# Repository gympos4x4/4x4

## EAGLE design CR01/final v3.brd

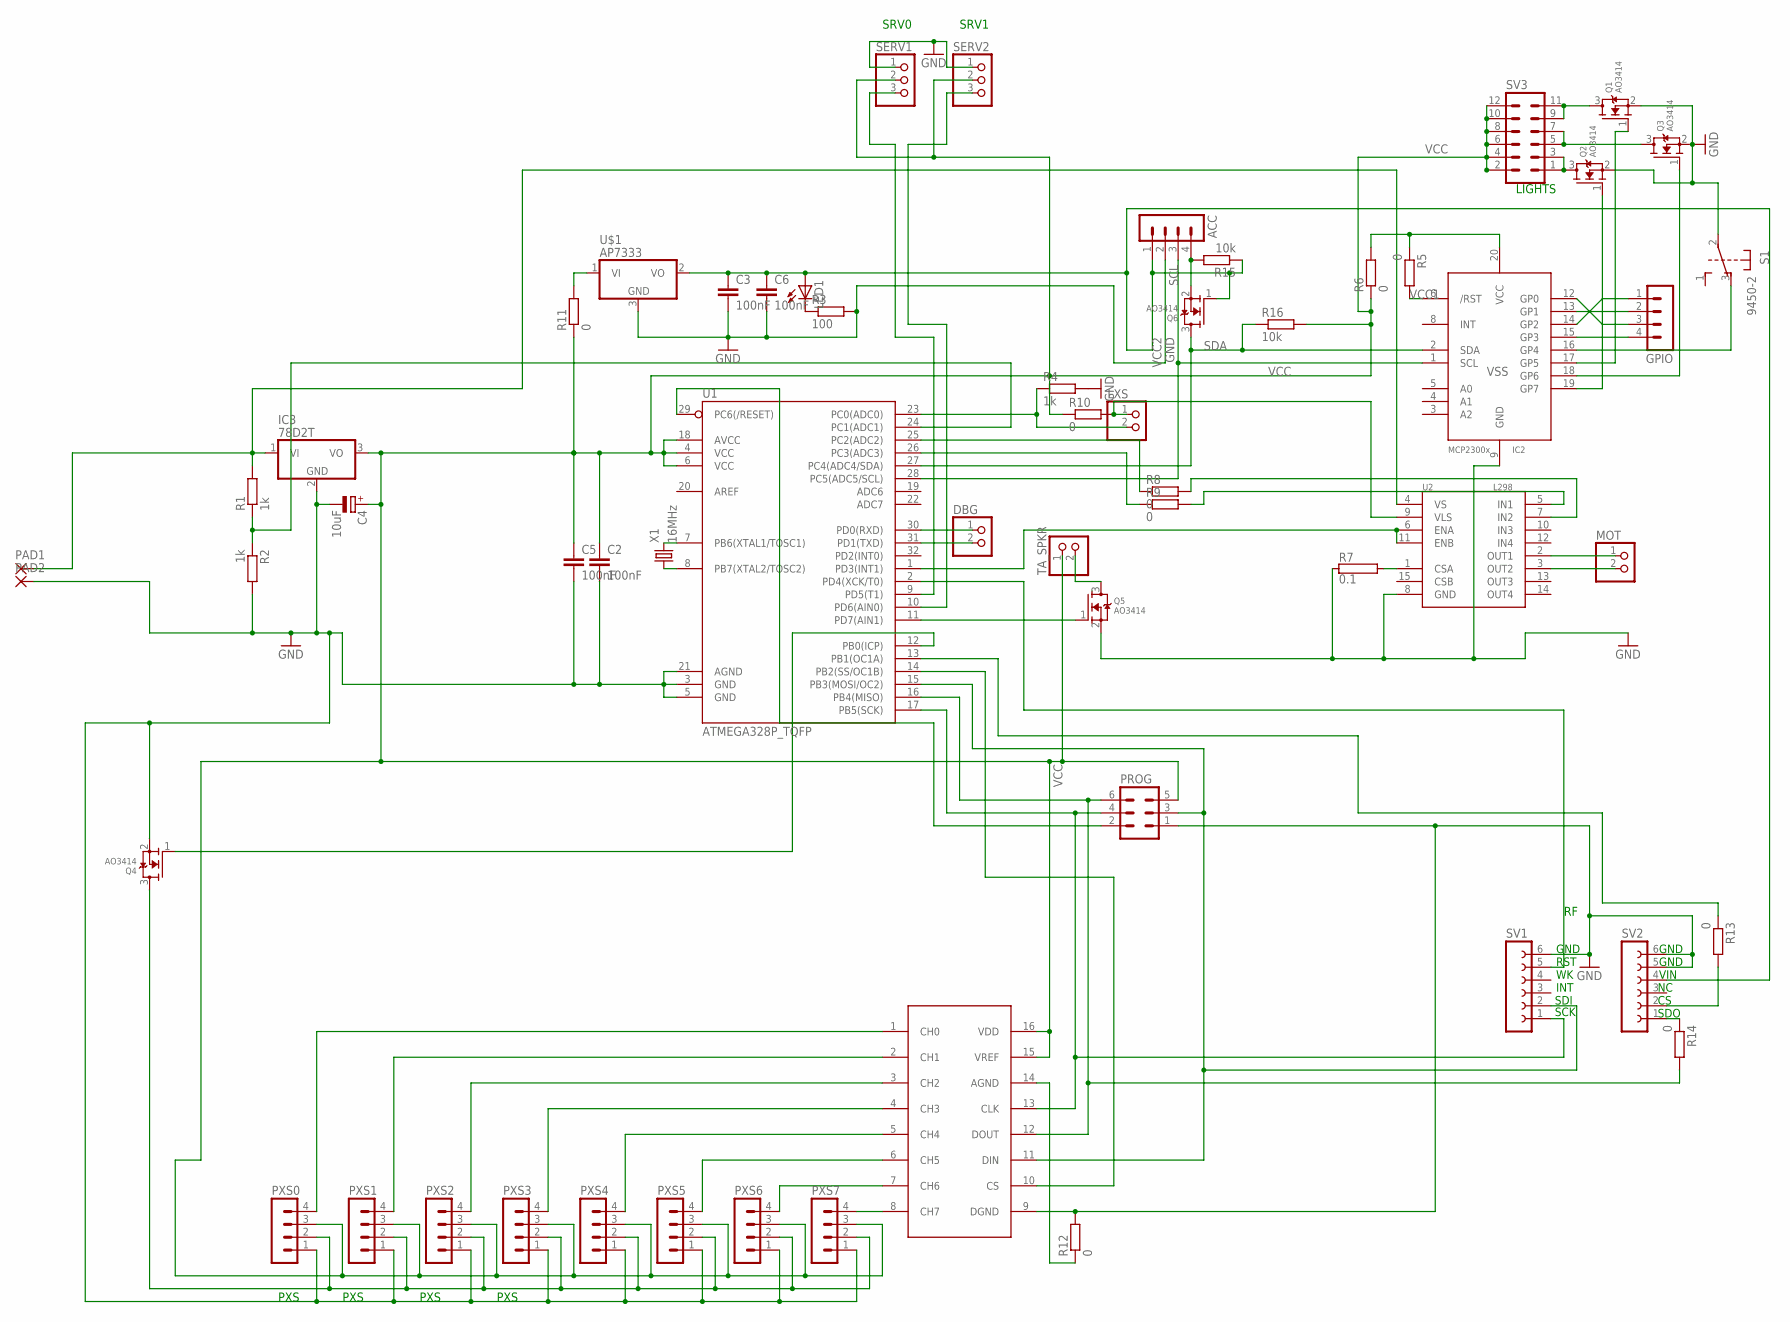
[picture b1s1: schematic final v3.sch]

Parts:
ACC: MA04-1
C2, C3, C5, C6: 100nF; C1206
C4: 10uF; 153CLV-0505
DBG: PINHD-1X2; 1X02
GPIO: MA04-1
IC2: MCP23008/SS; SSOP20
IC3: 78D2T; D2PACK
LED1: LEDCHIPLED_0603; CHIPLED_0603
LXS: PINHD-1X2; 1X02
MOT: PINHD-1X2; 1X02
PAD1, PAD2: SMD5; SMD2,54-5,08
PROG: MA03-2
PXS0, PXS1, PXS2, PXS3, PXS4, PXS5, PXS6, PXS7: MA04-1
Q1, Q2, Q3, Q4, Q5, Q6: AO3414; SOT23
R1, R4: 1k; M1206
R2: 1k; R1206
R3: 100; R0603
R5, R6, R8, R9, R10, R11, R12, R13, R14: 0; R0805BR
R7: 0.1; KH208R-8
R15, R16: 10k; R0805BR
S1: 9450-2
SERV1, SERV2: PINHD-1X3; 1X03
SV1, SV2: FE06-1; FE06
SV3: MA06-2
TA_SPKR: PINHD-1X2; 1X02
U1: ATMEGA328P_TQFP; TQFP32-08
U2: L298; MULTIWATT15
U$1: AP7333; SOT23
U$3: MCP3208; SO-16
X1: 16MHz; HC49/S

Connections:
!RST: PROG.2, U1.29 (PC6(/RESET))
GND: ACC.2, C2.2, C3.2, C4.-, C5.2, C6.2, IC2.9 (GND), IC3.2 (GND), PAD2.1, PROG.1, PXS0.1, PXS1.1, PXS2.1, PXS3.1, PXS4.1, PXS5.1, PXS6.1, PXS7.1, Q1.2 (S), Q2.2 (S), Q3.2 (S), Q4.2 (S), Q5.2 (S), R2.2, R3.2, R4.2, R7.1, R12.2, S1.2, SERV1.1, SERV2.1, SV1.6, SV2.5, SV2.6, U1.3 (GND), U1.5 (GND), U1.21 (AGND), U2.8 (GND), U$1.3 (GND), U$3.9 (DGND)
MISO: PROG.6, R14.2, U1.16 (PB4(MISO)), U$3.12 (DOUT)
MOSI: PROG.3, SV1.2, U1.15 (PB3(MOSI/OC2)), U$3.11 (DIN)
M_EN: U1.1 (PD3(INT1)), U2.6 (ENA), U2.11 (ENB)
M_IN1: R8.2, U2.7 (IN2)
M_IN2: R9.1, U1.26 (PC3(ADC3))
unnamed: Q5.1 (G), U1.11 (PD7(AIN1))
unnamed: Q5.3 (D), TA_SPKR.2
unnamed: U1.14 (PB2(SS/OC1B)), U$3.10 (CS)
unnamed: Q1.3 (D), SV3.9, SV3.11
unnamed: DBG.1, U1.30 (PD0(RXD))
unnamed: PXS7.4, U$3.8 (CH7)
unnamed: MOT.1, U2.2 (OUT1)
unnamed: PXS6.4, U$3.7 (CH6)
unnamed: PXS5.4, U$3.6 (CH5)
unnamed: DBG.2, U1.31 (PD1(TXD))
unnamed: PXS4.4, U$3.5 (CH4)
unnamed: PXS3.4, U$3.4 (CH3)
unnamed: PXS2.4, U$3.3 (CH2)
unnamed: PXS1.4, U$3.2 (CH1)
unnamed: Q3.3 (D), SV3.5, SV3.7
unnamed: PXS0.4, U$3.1 (CH0)
unnamed: Q2.3 (D), SV3.1, SV3.3
unnamed: LXS.2, R4.1, U1.23 (PC0(ADC0))
unnamed: Q4.1 (G), U1.12 (PB0(ICP))
unnamed: PXS0.2, PXS1.2, PXS2.2, PXS3.2, PXS4.2, PXS5.2, PXS6.2, PXS7.2, Q4.3 (D)
unnamed: ACC.4, Q6.2 (S), R15.2
unnamed: MOT.2, U2.3 (OUT2)
unnamed: LED1.C, R3.1
unnamed: R8.1, U1.25 (PC2(ADC2))
unnamed: R9.2, U2.5 (IN1)
unnamed: SV1.5, U1.2 (PD4(XCK/T0))
unnamed: IC2.20 (VCC), R5.1, R6.2
unnamed: SERV1.3, U1.9 (PD5(T1))
unnamed: U1.7 (PB6(XTAL1/TOSC1)), X1.2
unnamed: IC2.19 (GP7), Q2.1 (G)
unnamed: SERV2.3, U1.10 (PD6(AIN0))
unnamed: IC2.17 (GP5), Q1.1 (G)
unnamed: IC2.18 (GP6), Q3.1 (G)
unnamed: U1.8 (PB7(XTAL2/TOSC2)), X1.1
unnamed: R7.2, U2.1 (CSA)
unnamed: IC2.16 (GP4), S1.3 (O)
unnamed: GPIO.3, IC2.12 (GP0)
unnamed: GPIO.2, IC2.13 (GP1)
unnamed: GPIO.1, IC2.14 (GP2)
unnamed: GPIO.4, IC2.15 (GP3)
unnamed: R11.2, U$1.1 (VI)
unnamed: R12.1, U$3.14 (AGND)
unnamed: R14.1, SV2.1
unnamed: R13.2, SV2.2
RF_CS: R13.1, U1.13 (PB1(OC1A))
SCK: PROG.4, SV1.1, U1.17 (PB5(SCK)), U$3.13 (CLK)
SCL: ACC.3, IC2.1 (SCL), U1.28 (PC5(ADC5/SCL))
SDA: IC2.2 (SDA), Q6.3 (D), R16.1, U1.27 (PC4(ADC4/SDA))
VBATT: R1.1, R2.1, U1.24 (PC1(ADC1))
VCC: C2.1, C4.+, C5.1, IC3.3 (VO), PROG.5, PXS0.3, PXS1.3, PXS2.3, PXS3.3, PXS4.3, PXS5.3, PXS6.3, PXS7.3, R6.1, R10.1, R11.1, R16.2, SERV1.2, SERV2.2, SV3.2, SV3.4, SV3.6, SV3.8, SV3.10, SV3.12, TA_SPKR.1, U1.4 (VCC), U1.6 (VCC), U1.18 (AVCC), U$3.15 (VREF), U$3.16 (VDD)
VCC0: LXS.1, R10.2, U2.9 (VLS)
VCC1: IC2.6 (/RST), R5.2
VCC2: ACC.1, C3.1, C6.1, LED1.A, Q6.1 (G), R15.1, SV2.4, U$1.2 (VO)
VSS: IC3.1 (VI), PAD1.1, R1.2, U2.4 (VS)

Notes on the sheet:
GND
RST
VIN
SDO
INT
SDI
SCK
SRV0
SRV1
PXS
LIGHTS

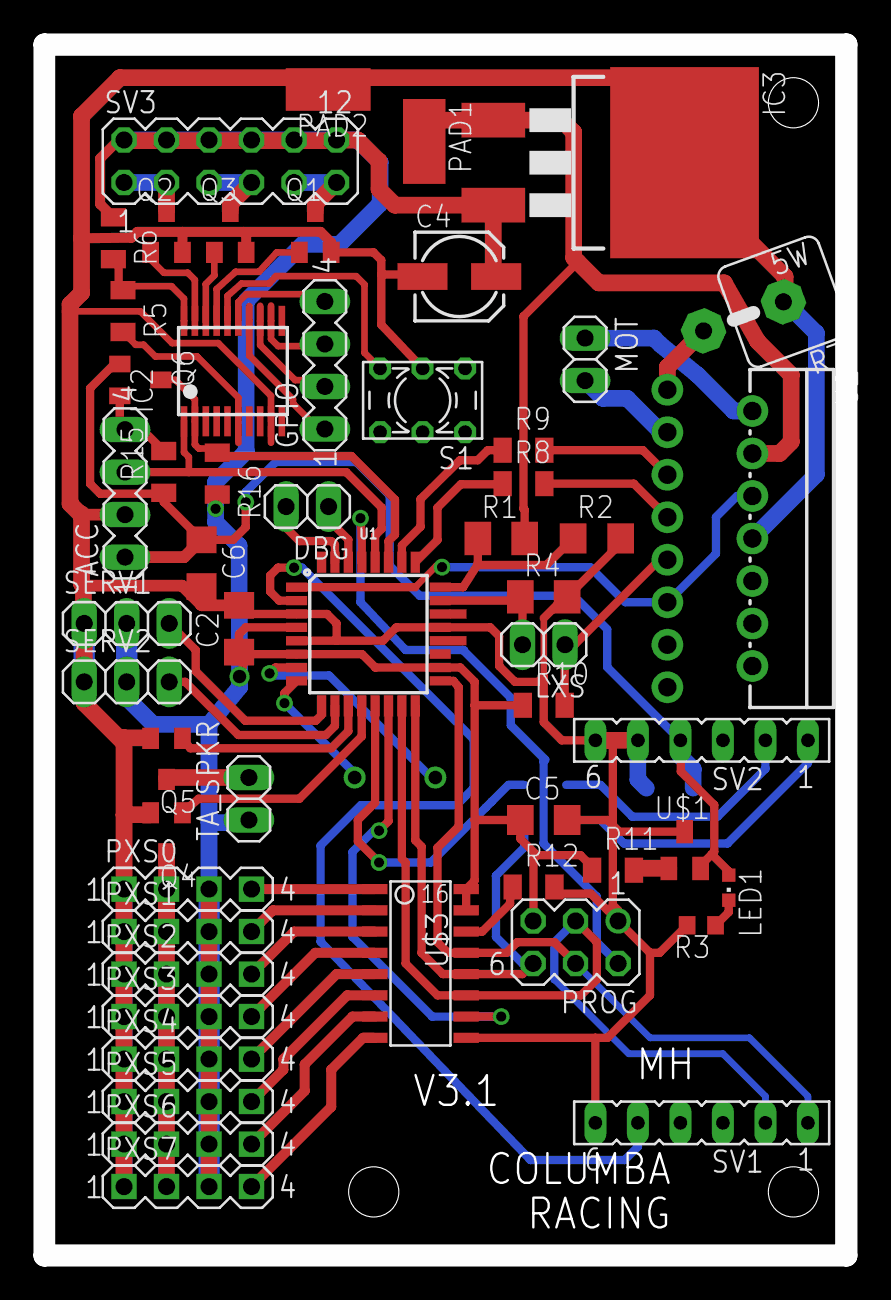
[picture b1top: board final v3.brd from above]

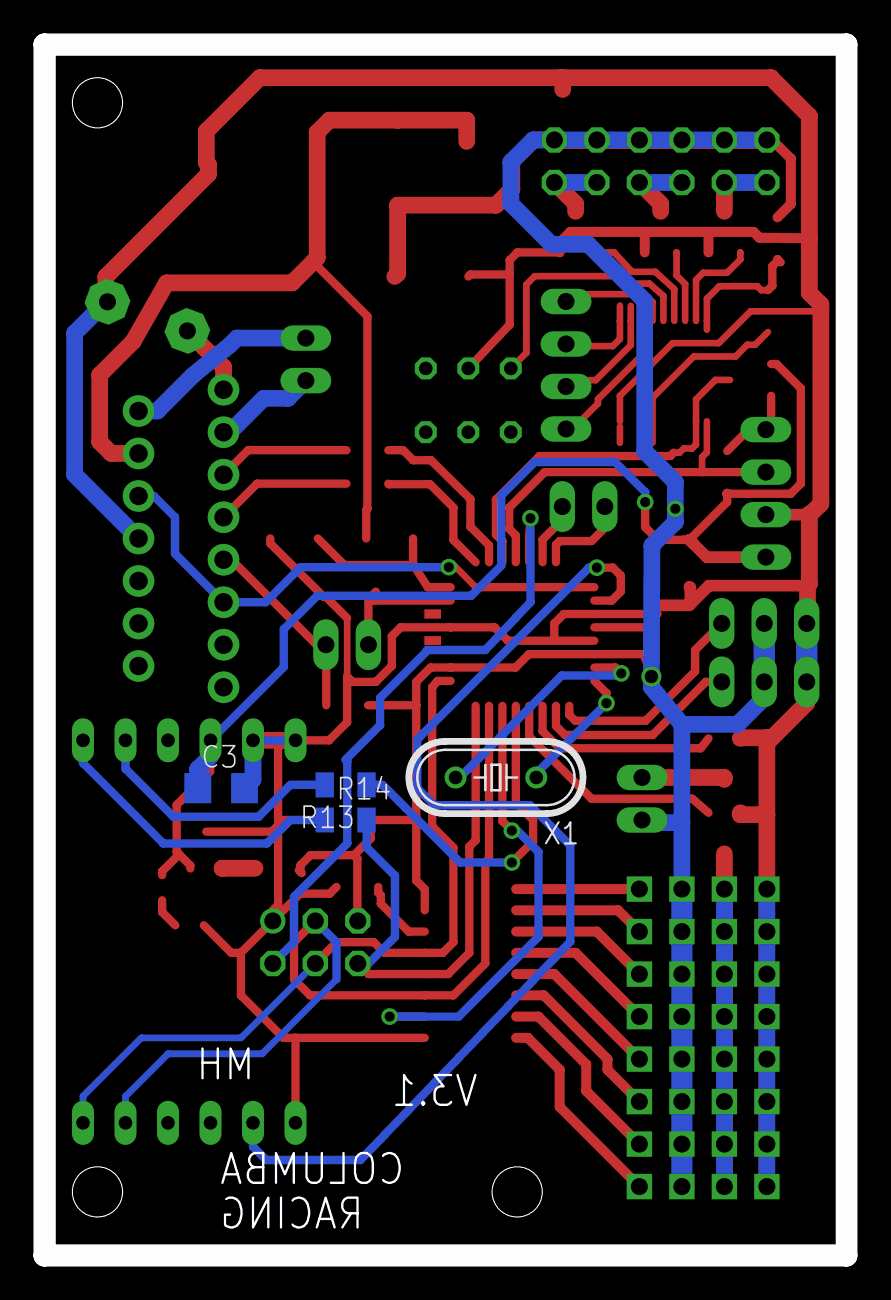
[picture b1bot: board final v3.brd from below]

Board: 2 copper layers, 47.9 x 72.4 mm, 58 parts (4 on the bottom side), 61 nets.

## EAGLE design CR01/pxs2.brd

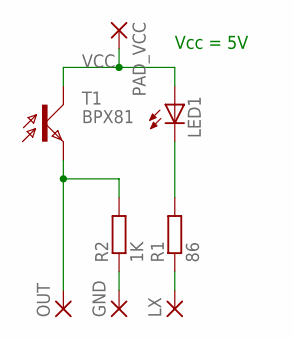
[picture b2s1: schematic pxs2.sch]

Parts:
GND: SMD2; SMD1,27-2,54
LED1: LED5MM
LX: SMD2; SMD1,27-2,54
OUT: SMD2; SMD1,27-2,54
PAD_VCC: SMD2; SMD1,27-2,54
R1: 86; 0207/2V
R2: 1K; R1206
T1: BPX81

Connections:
GND: GND.1, R2.1
unnamed: LX.1, R1.1
unnamed: LED1.K (C), R1.2
OUT: OUT.1, R2.2, T1.E
VCC: LED1.A, PAD_VCC.1, T1.C

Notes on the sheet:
Vcc = 5V

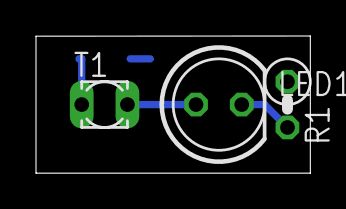
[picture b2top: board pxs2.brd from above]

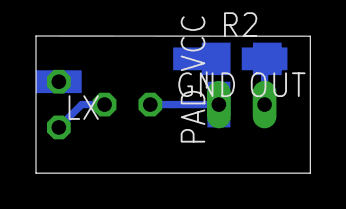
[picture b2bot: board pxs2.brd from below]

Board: 2 copper layers, 15.2 x 7.6 mm, 8 parts (5 on the bottom side), 5 nets.

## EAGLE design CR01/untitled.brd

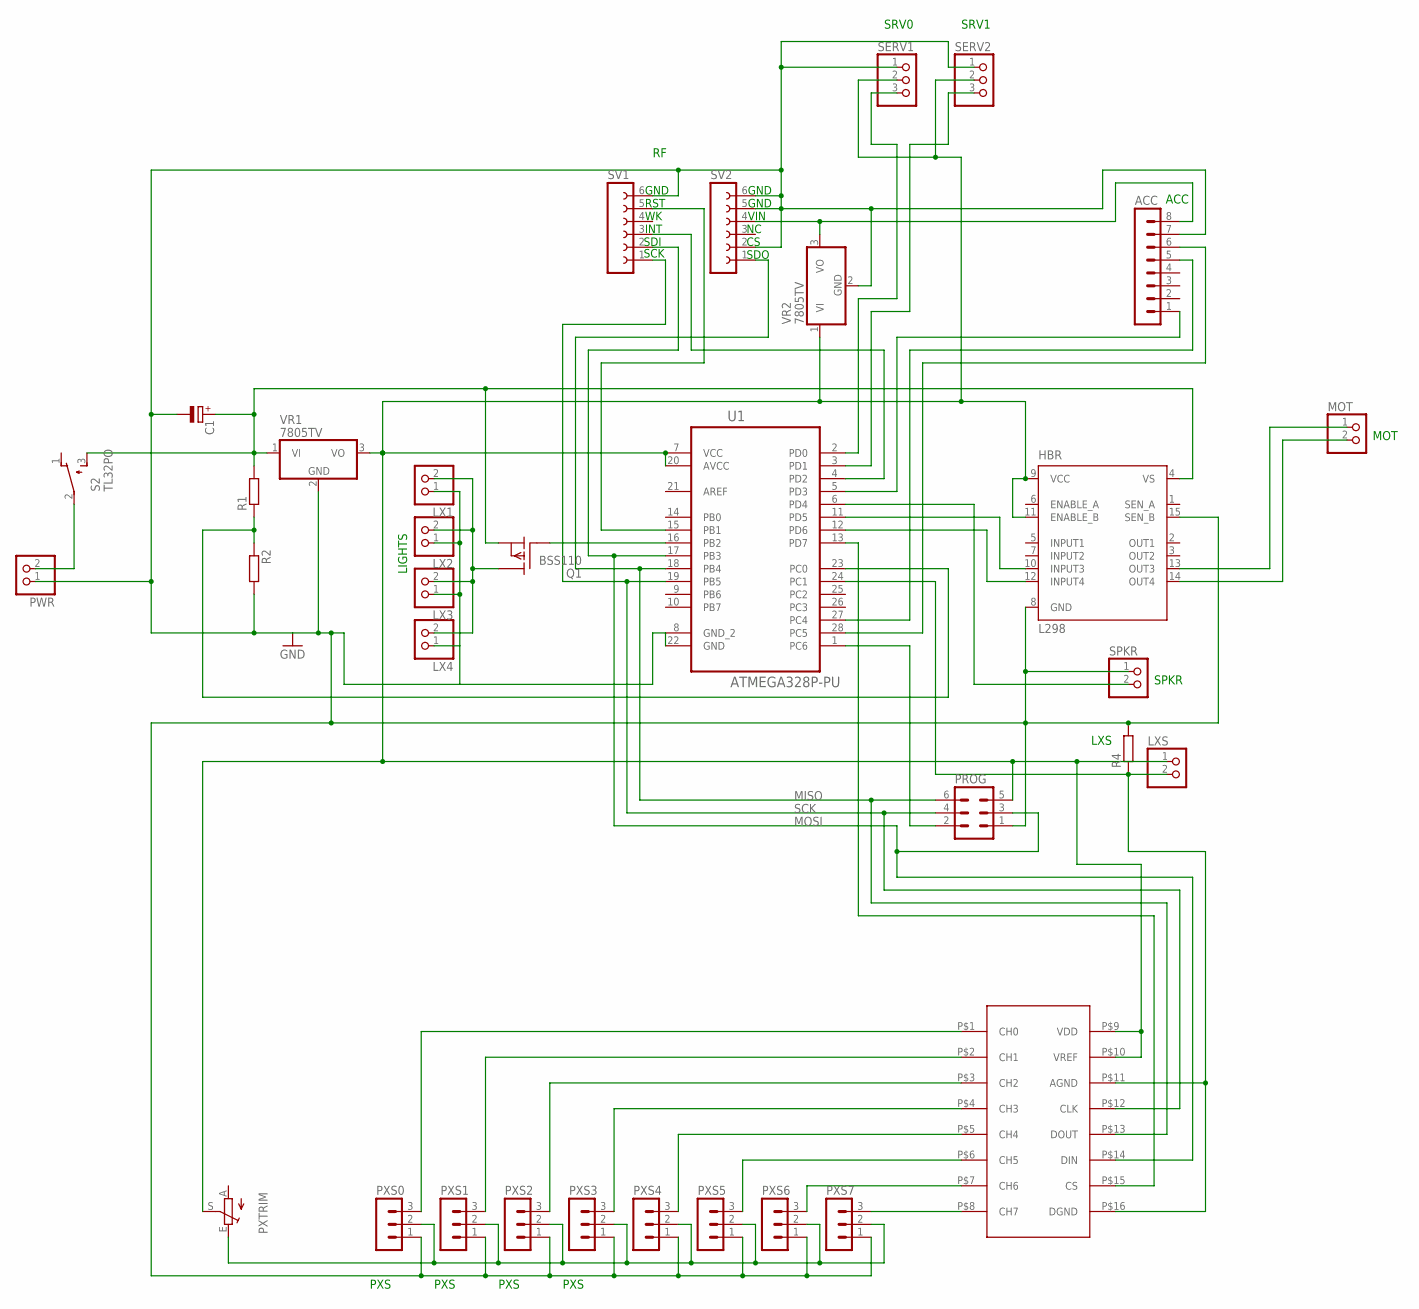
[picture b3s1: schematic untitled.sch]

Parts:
ACC: MA08-1
C1: CPOL-EUE2.5-7; E2,5-7
HBR: L298; MULTIWATT-15
LX1, LX2, LX3, LX4: PINHD-1X2; 1X02
LXS: PINHD-1X2; 1X02
MOT: PINHD-1X2; 1X02
PROG: MA03-2
PWR: PINHD-1X2; 1X02
PXS0, PXS1, PXS2, PXS3, PXS4, PXS5, PXS6, PXS7: MA03-1
PXTRIM: TRIM_EU-CA9V; CA9V
Q1: BSS110; TO92
R1, R2, R4: R-EU_0309/V; 0309V
S2: TL32PO; TL3XPO
SERV1, SERV2: PINHD-1X3; 1X03
SPKR: PINHD-1X2; 1X02
SV1, SV2: FE06-1; FE06
U1: ATMEGA328P-PU; DIP254P762X457-28
U$1: MCP3208; DIP16
VR1, VR2: 7805TV; TO220V

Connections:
GND: ACC.7, C1.-, HBR.8 (GND), HBR.15 (SEN_B), LX1.1, LX2.1, LX3.1, LX4.1, PROG.1, PWR.1, PXS0.1, PXS1.1, PXS2.1, PXS3.1, PXS4.1, PXS5.1, PXS6.1, PXS7.1, R2.2, R4.2, SERV1.1, SERV2.1, SPKR.1, SV1.6, SV2.2, SV2.5, SV2.6, U1.8 (GND_2), U1.22 (GND), VR1.2 (GND), VR2.2 (GND)
MISO: PROG.6, SV2.1, U1.18 (PB4), U$1.P$13 (DOUT)
MOSI: PROG.3, SV1.2, U1.17 (PB3), U$1.P$14 (DIN)
unnamed: R1.1, R2.1, U1.23 (PC0)
unnamed: U1.13 (PD7), U$1.P$15 (CS)
unnamed: SERV1.3, U1.2 (PD0)
unnamed: HBR.13 (OUT3), MOT.1
unnamed: HBR.14 (OUT4), MOT.2
unnamed: PXS7.3, U$1.P$8 (CH7)
unnamed: HBR.12 (INPUT4), U1.12 (PD6)
unnamed: PXS6.3, U$1.P$7 (CH6)
unnamed: PXS5.3, U$1.P$6 (CH5)
unnamed: ACC.6, U1.28 (PC5)
unnamed: PXS4.3, U$1.P$5 (CH4)
unnamed: PXS3.3, U$1.P$4 (CH3)
unnamed: PXS2.3, U$1.P$3 (CH2)
unnamed: PXS1.3, U$1.P$2 (CH1)
unnamed: ACC.5, U1.27 (PC4)
unnamed: PXS0.3, U$1.P$1 (CH0)
unnamed: ACC.1, U1.5 (PD3)
unnamed: HBR.10 (INPUT3), U1.11 (PD5)
unnamed: PXS0.2, PXS1.2, PXS2.2, PXS3.2, PXS4.2, PXS5.2, PXS6.2, PXS7.2, PXTRIM.E
unnamed: SERV2.3, U1.3 (PD1)
unnamed: Q1.2 (G), U1.16 (PB2)
unnamed: SPKR.2, U1.6 (PD4)
unnamed: LXS.2, R4.1, U1.24 (PC1), U$1.P$11 (AGND), U$1.P$16 (DGND)
unnamed: LX1.2, LX2.2, LX3.2, LX4.2, Q1.3 (D)
RST: PROG.2, U1.1 (PC6)
R_INT: SV1.3, U1.4 (PD2)
R_RST: SV1.5, U1.15 (PB1)
SCK: PROG.4, SV1.1, U1.19 (PB5), U$1.P$12 (CLK)
V3V: ACC.8, SV2.4, VR2.3 (VO)
VCC: HBR.9 (VCC), HBR.11 (ENABLE_B), LXS.1, PROG.5, PXTRIM.S, SERV1.2, SERV2.2, U1.7 (VCC), U1.20 (AVCC), U$1.P$9 (VDD), U$1.P$10 (VREF), VR1.3 (VO), VR2.1 (VI)
VSS: C1.+, HBR.4 (VS), Q1.1 (S), R1.2, S2.3 (S), VR1.1 (VI)
VSS_IN: PWR.2, S2.2

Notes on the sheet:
MOT
GND
RST
VIN
SDO
INT
SDI
SCK
SRV0
SRV1
ACC
SPKR
PXS
LXS
LIGHTS

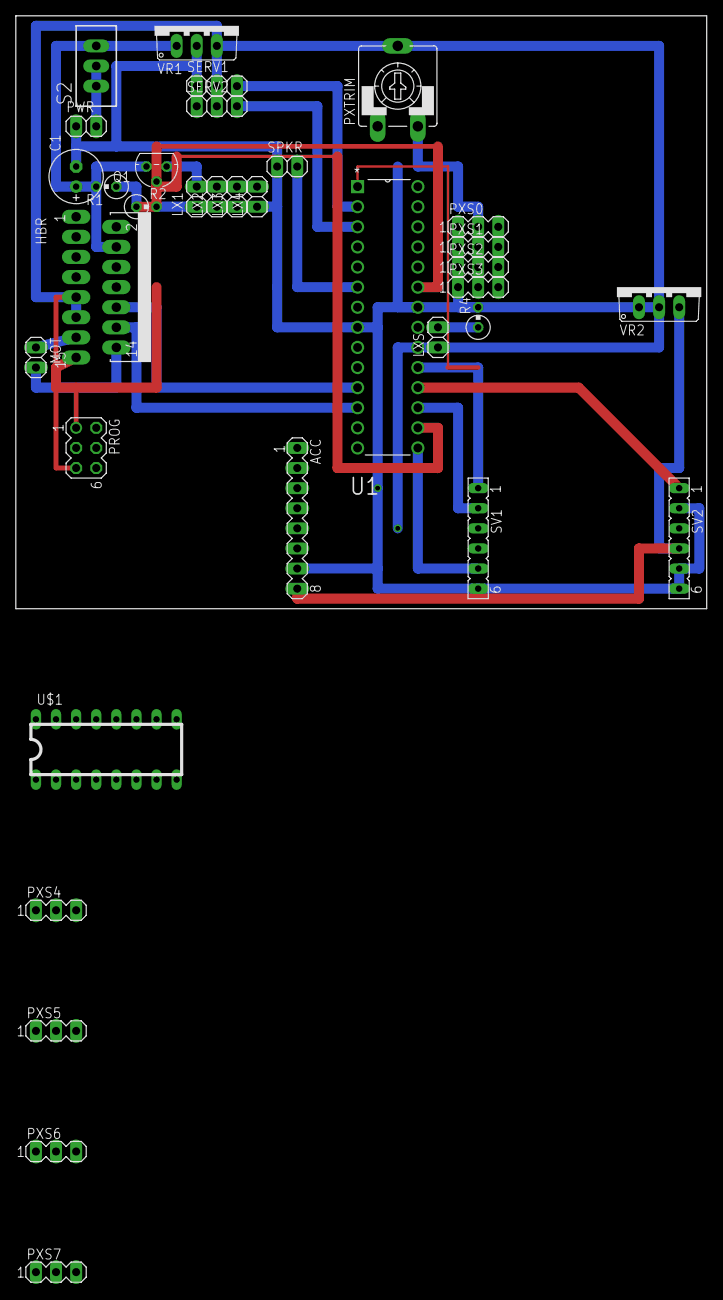
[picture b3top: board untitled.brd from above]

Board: 2 copper layers, 87.3 x 74.9 mm, 34 parts (0 on the bottom side), 35 nets.

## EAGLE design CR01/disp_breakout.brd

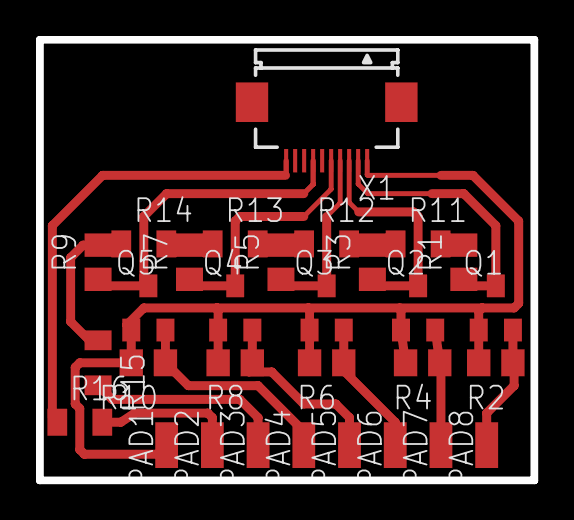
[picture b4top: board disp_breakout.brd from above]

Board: 2 copper layers, 27.5 x 24.5 mm, 30 parts (0 on the bottom side), 19 nets.

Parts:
PAD1: Vcc; SMD1,27-2,54
PAD2: GND; SMD1,27-2,54
PAD3: Vdd; SMD1,27-2,54
PAD4: PD; SMD1,27-2,54
PAD5: CS; SMD1,27-2,54
PAD6: MOSI; SMD1,27-2,54
PAD7: MISO; SMD1,27-2,54
PAD8: SCK; SMD1,27-2,54
Q1, Q2, Q3, Q4, Q5: AO3414; SOT23
R1, R2, R3, R4, R5, R6, R7, R8, R9, R10: 10k; R0805
R11, R12, R13, R14, R15, R16: 0; R0805BR
X1: FH12-10S-0.5SH

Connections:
CSH: PAD5.1, Q4.2, R8.1
CSL: Q4.3, R7.1, X1.5
GND: R16.1, X1.10
GND0: PAD2.1, R16.2
MISOH: PAD7.1, Q2.2, R4.1
MISOL: Q2.3, R3.1, X1.3
MOSIH: PAD6.1, Q3.2, R6.1
MOSIL: Q3.3, R5.1, X1.4
PDH: PAD4.1, Q5.2, R10.1
PDL: Q5.3, R9.1, X1.7
SCKH: PAD8.1, Q1.2, R2.1
SCKL: Q1.3, R1.1, X1.2
VCC: PAD1.1, Q1.1, Q2.1, Q3.1, Q4.1, Q5.1, R2.2, R4.2, R6.2, R8.2, R10.2, X1.1
VDD: R1.2, R11.2
VDD0: PAD3.1, R15.2
VDD1: R3.2, R11.1, R12.2
VDD2: R5.2, R12.1, R13.2
VDD3: R7.2, R13.1, R14.2
VDD4: R9.2, R14.1, R15.1

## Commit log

2016-12-26 Added communication system
2016-12-27 added .gitignore to Car
2016-12-27 removed old Car project
2016-12-27 finally removed old Car project
2016-12-27 created new Car project
2016-12-27 added TiltAlarm to Car project
2016-12-27 added Lights to Car project
2016-12-27 updated library in Car project
2017-01-04 Reworked directory structure, content is the same. Now it builds fine.
2017-04-28 Got rid of double in TiltAlarm.h
2017-06-26 added eADC and ParkingSensors libraries
2017-06-26 reformated ParkingSensors library
2017-06-26 added SteeringControl library
2017-09-01 Trying to make SyncManager work. Probably will need complete rewrite.
2017-09-01 Changes to SyncManager
2017-09-07 Rewrote SharedLibrary and SyncManager. Rewrote TiltAlartm
2017-09-07 trying to make it compile - 1
2017-09-07 IT COMPILES!!!
2017-10-13 Changed gitignore - added .vcxproj
2017-10-20 Update MotorControl.h
    Pridané meno autora
2017-10-20 Updated local libraries for car
2017-10-22 Updated pins
2017-10-22 Added new project for car
2017-10-22 Pridaná premenná battery_percentage
    Line 13
2017-10-22 Pridaná premenná battery_percentage
    line 97,110
2017-10-22 changed DATA SYNC logic, so we don't have to manually edit it. needs testing.
2017-10-22 logic tested, works.
2017-10-23 Added libraries to NewCar project
2017-10-23 Fixed library
2017-10-24 added eagle files
2017-10-24 edited gitignore, added eagle project file
2017-10-24 updated board
2017-10-24 testing symlink
2017-10-25 compiles, should work. needs testing
2017-10-25 updated gitignore
2017-10-25 update pcb (removed CAM files)
2017-10-25 added libraries that had been moved
2017-10-25 Revert "added libraries that had been moved"
    This reverts commit 5cd370acf8229085d68a5e55d2c00684370b810e.
2017-10-25 update atmel studio project
2017-10-25 use c++11
2017-10-25 don't use =default
2017-10-25 don't use auto& to anonymous struct
2017-10-25 should be compiled project, but not sure about it
2017-10-28 Updated PCB and Schematic for V2.1
2017-10-31 changed types in ParkingSensor lib to signed
2017-11-06 Updated pins, so they match the specification
2017-11-07 more updated pins. MotorControl.h needs to be checked
2017-11-07 Changed parking data that need to be sent to the controller
2017-11-07 Added controller project
    FT800 display library: http://www.ftdichip.com/Support/SoftwareExamples/FT800_Projects.htm#Arduino_Specific
2017-11-07 1) switched to arduino 1.0.5-rc2 2) we do not need to have display library installed 3) removed (hopefully) redundant mrf24j_c - old and doesn't match with online version
2017-11-07 added rf to controller + misc optimisations
2017-11-09 Added controller testing program, reworked motor control library, perormed some unsuccessful testing
2017-11-10 much change such wow
2017-11-11 Apdated pins and code to match V2 board
2017-11-11 Fixed bugs in ControllerDisplay and added mrf24j lib to project file
2017-11-11 reworked RF communication
2017-11-12 Fixed bug in rear parking sensors display
2017-11-12 Added signal indicator
2017-11-12 Fixed library include in ControllerDisplay lib
2017-11-12 Removed unnecessary Serial print
2017-11-12 Added no signal indicator
2017-11-12 Bugfix
2017-11-12 added PXS2 schematic
2017-11-14 updated Rf communcation
2017-11-14 use the same versions of MRF library
2017-11-14 hmeh, doesn't work. dunno why.
2017-11-15 next update among many
2017-11-15 I think that I've updated pins in this commit
2017-11-16 car and controller update
2017-11-16 Revert "I think that I've updated pins in this commit"
    This reverts commit 3bf91be540f8f1bf9c59201f7335c8891c011833.
2017-11-18 not many times left but hope not lost
2017-11-19 SPI communication between ESP and Arduino
2017-11-19 final
2017-11-19 Added ProxiDemo
    (Proximity alarm)
    Beware, this is a raw AVR program - might induce anxiety upon reading.
2017-11-24 Added final car
2017-11-25 added V3 board
2017-11-27 Board update
2017-11-27 Fixed tilt sensor
2017-11-28 Added MCP23008 lib to FinalCarProject
2017-12-03 Revert "changes"
    This reverts commit 56039cf7a3f40da9b877b3a95c0970397c23af20.
2017-12-05 such compile much wow
2017-12-05 Added manual (de)activation of lights
    I am not aware why so many files have changed, i edited only lights.cpp & .h
2017-12-05 added channel selection
2017-12-06 last light
2017-12-07 an end, once and for all
2018-05-06 safety commit before cleanup
2018-05-14 add v3

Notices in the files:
parts and their libraries:
SparkFun-IC-Microcontroller: Licensing: Creative Commons ShareAlike 4.0 International - https://creativecommons.org/licenses/by-sa/4.0
